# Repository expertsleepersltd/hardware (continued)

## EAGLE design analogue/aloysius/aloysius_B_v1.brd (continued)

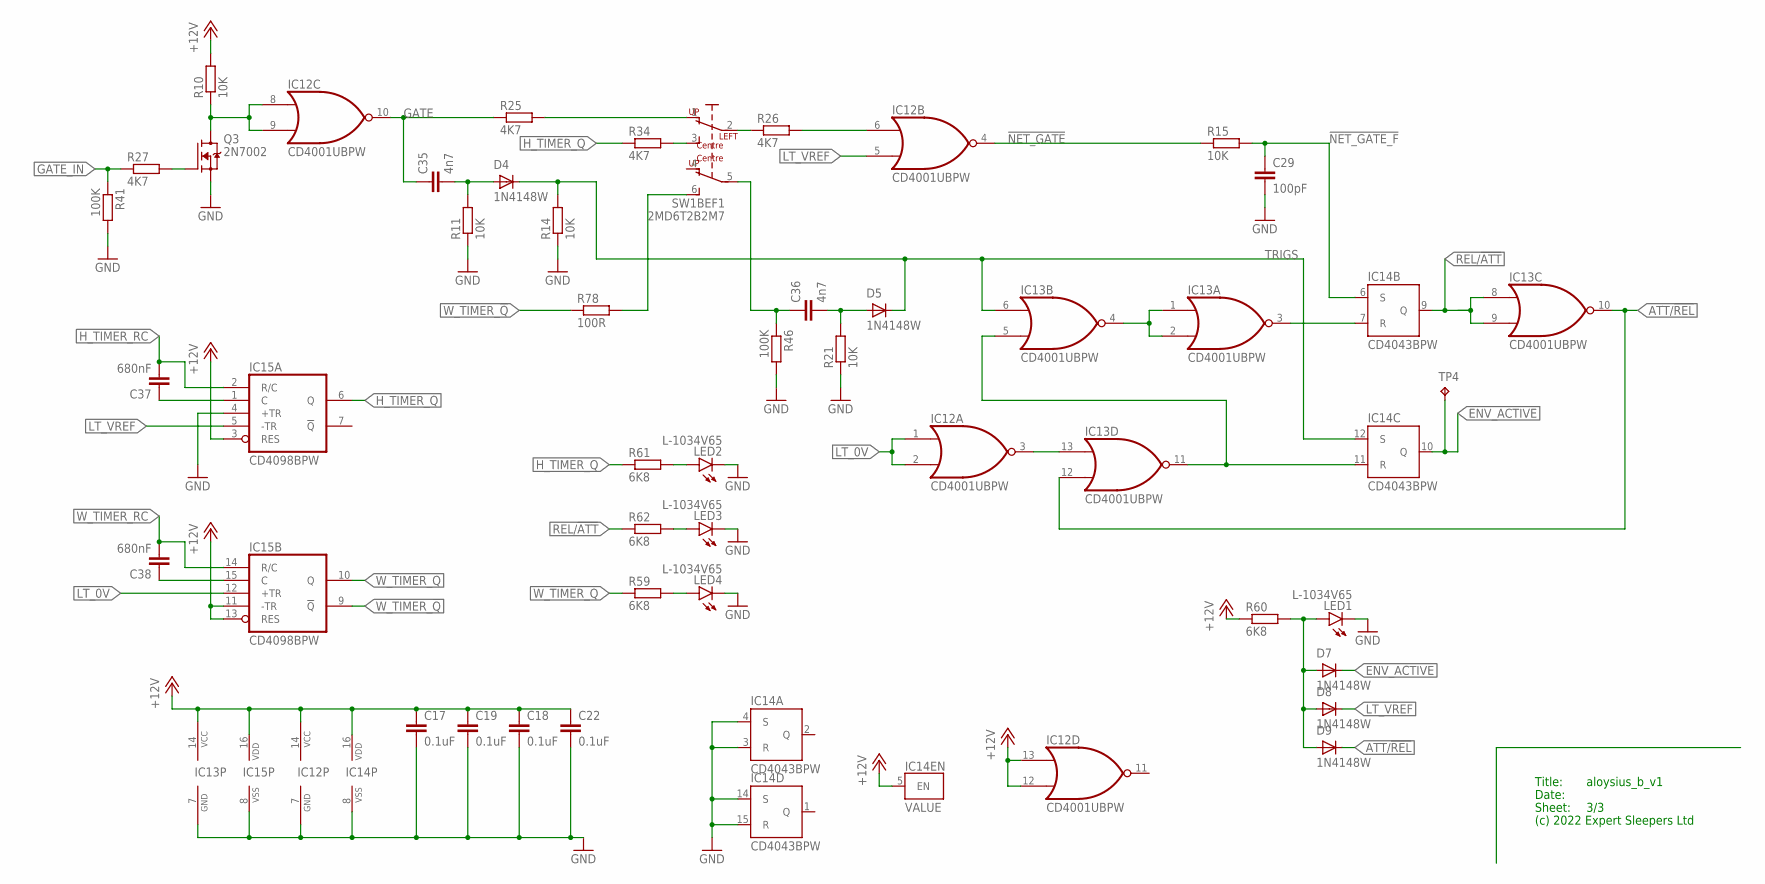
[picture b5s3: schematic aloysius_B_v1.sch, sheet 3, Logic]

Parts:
C17, C18, C19, C22: 0.1uF; C0402
C29: 100pF; C0603
C35, C36: 4n7; C0603
C37, C38: 680nF; C0603
D4, D5, D7, D8, D9: 1N4148W; SOD123
IC12, IC13: CD4001UBPW; TSSOP14
IC14: CD4043BPW; TSSOP16
IC15: CD4098BPW; TSSOP16
LED1, LED2, LED3, LED4: L-1034V65; L-1034_V6.5MM
Q3: 2N7002; SOT23
R10, R11, R14, R15, R21: 10K; R0603
R25, R26, R27, R34: 4K7; R0603
R41, R46: 100K; R0603
R59, R60, R61, R62: 6K8; R0603
R78: 100R; R0603
SW1: 2MD6T2B2M7; 2MD1T2B2M7RE
TP4: RA2; P1-13

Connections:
!NET_GATE: IC12.4 (O), R15.1
!NET_GATE_F: C29.1, IC14.6 (S), R15.2
+12V: C17.1, C18.1, C19.1, C22.1, IC12.12 (I1), IC12.13 (I0), IC12.14 (VCC), IC13.14 (VCC), IC14.5 (EN), IC14.16 (VDD), IC15.3 (RES), IC15.11 (-TR), IC15.13 (RES), IC15.16 (VDD), R10.2, R60.1; also elsewhere on the board
ATT/!REL: D9.C, IC13.10 (O), IC13.12 (I1); also elsewhere on the board
ENV_ACTIVE: D7.C, IC14.10 (Q), TP4.TP; also elsewhere on the board
GATE: C35.1, IC12.10 (O), R25.1
GATE_IN: R27.1, R41.1; also elsewhere on the board
GATE_SW: R25.2, SW1.1 (LU)
GND: C17.2, C18.2, C19.2, C22.2, C29.2, IC12.7 (GND), IC13.7 (GND), IC14.3 (R), IC14.4 (S), IC14.8 (VSS), IC14.14 (S), IC14.15 (R), IC15.4 (+TR), IC15.8 (VSS), LED1.K (C), LED2.K (C), LED3.K (C), LED4.K (C), Q3.2 (S), R11.1, R14.1, R21.1, R41.2, R46.2; also elsewhere on the board
H_TIMER_Q: IC15.6 (Q), R34.1, R61.1
H_TIMER_RC: C37.2, IC15.2 (R/C); also elsewhere on the board
LT_0V: IC12.1 (I0), IC12.2 (I1), IC15.12 (+TR); also elsewhere on the board
LT_VREF: D8.C, IC12.5 (I1), IC15.5 (-TR); also elsewhere on the board
unnamed: R34.2, SW1.3 (LD)
unnamed: C36.2, D5.A, R21.2
unnamed: C37.1, IC15.1 (C)
unnamed: IC12.6 (I0), R26.2
unnamed: IC12.3 (O), IC13.13 (I0)
unnamed: C38.1, IC15.15 (C)
unnamed: LED4.A, R59.2
unnamed: C35.2, D4.A, R11.2
unnamed: IC12.8 (I0), IC12.9 (I1), Q3.3 (D), R10.1
unnamed: Q3.1 (G), R27.2
unnamed: R26.1, SW1.2 (PL)
unnamed: IC13.3 (O), IC14.7 (R)
unnamed: LED2.A, R61.2
unnamed: IC13.5 (I1), IC13.11 (O), IC14.11 (R)
unnamed: LED3.A, R62.2
unnamed: IC13.1 (I0), IC13.2 (I1), IC13.4 (O)
unnamed: D7.A, D8.A, D9.A, LED1.A, R60.2
REL/!ATT: IC13.8 (I0), IC13.9 (I1), IC14.9 (Q), R62.1; also elsewhere on the board
RETRIG: R78.2, SW1.6 (RD)
RETRIG_SW: C36.1, R46.1, SW1.5 (PR)
TRIGS: D4.C, D5.C, IC13.6 (I0), IC14.12 (S), R14.2
W_TIMER_!Q: IC15.9 (!Q), R78.1
W_TIMER_Q: IC15.10 (Q), R59.1
W_TIMER_RC: C38.2, IC15.14 (R/C); also elsewhere on the board

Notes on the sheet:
Title:
Date:
Sheet:
(c) 2022 Expert Sleepers Ltd

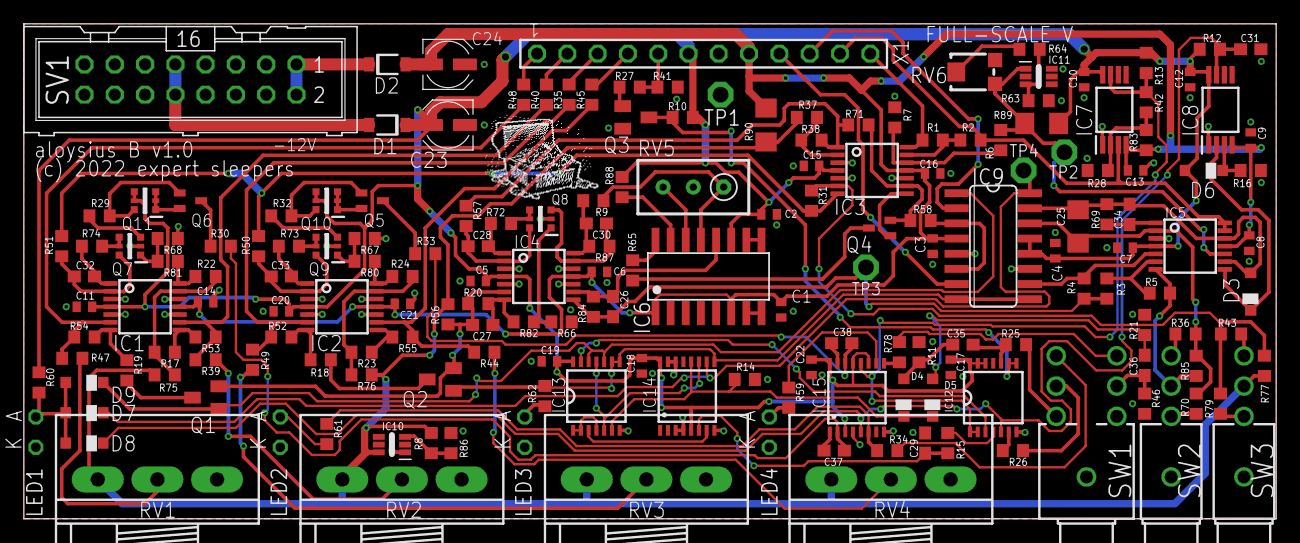
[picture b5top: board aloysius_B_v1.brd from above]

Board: 2 copper layers, 105.0 x 41.5 mm, 183 parts (0 on the bottom side), 126 nets.

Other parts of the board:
U$2: TREASURE_10MM_300DPI

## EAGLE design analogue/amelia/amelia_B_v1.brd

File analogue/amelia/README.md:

Amelia
======

https://expert-sleepers.co.uk/amelia.html

Copyright (c) 2023 Expert Sleepers Ltd

Please refer to [LICENSE.md](LICENSE.md) for licensing information.

Please note that Expert Sleepers® is a registered trade mark in the UK and the European Union. Remove any branding before making a derivative work.

Front panel layout is [here](../../panels).

Board and schematic are in [EAGLE](https://en.wikipedia.org/wiki/EAGLE_(program)) format.

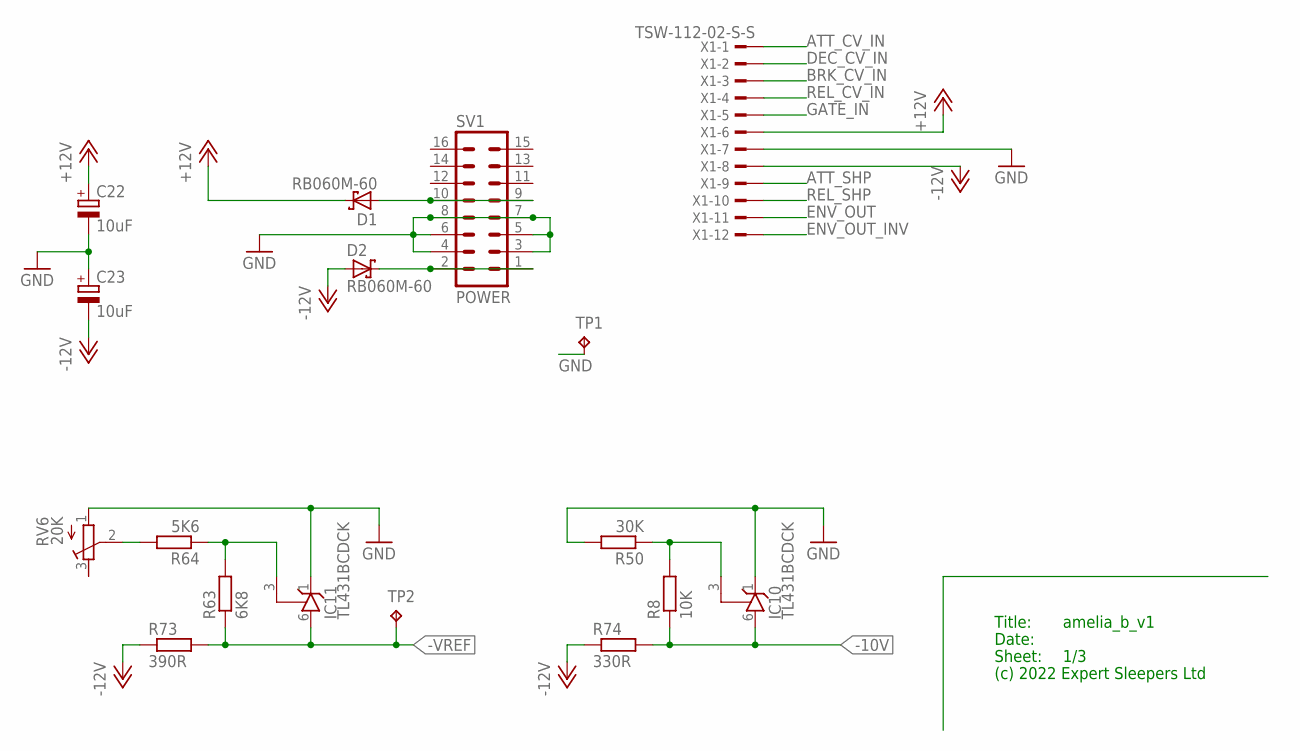
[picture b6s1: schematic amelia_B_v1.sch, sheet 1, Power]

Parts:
C22, C23: 10uF; UD-4X5,8_NICHICON
D1, D2: RB060M-60; SOD123FL
IC10, IC11: TL431BCDCK; DCK_SC-70
R8: 10K; R0603
R50: 30K; R0603
R63: 6K8; R0603
R64: 5K6; R0603
R73: 390R; R1206
R74: 330R; R1206
RV6: 20K; TC33X
SV1: POWER; ML16
TP1, TP2: RA2; P1-13
X1: TSW-112-02-S-S

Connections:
+12V: C22.+, D1.C, X1.6; also elsewhere on the board
-10V: IC10.6 (A), R8.1, R74.2; also elsewhere on the board
-12V: C23.-, D2.A, R73.1, R74.1, X1.8; also elsewhere on the board
-VREF: IC11.6 (A), R63.1, R73.2, TP2.TP; also elsewhere on the board
ATT_CV_IN: X1.1; also elsewhere on the board
ATT_SHP: X1.9; also elsewhere on the board
BRK_CV_IN: X1.3; also elsewhere on the board
DEC_CV_IN: X1.2; also elsewhere on the board
ENV_OUT: X1.11; also elsewhere on the board
ENV_OUT_INV: X1.12; also elsewhere on the board
GATE_IN: X1.5; also elsewhere on the board
GND: C22.-, C23.+, IC10.1 (C), IC11.1 (C), R50.2, RV6.1 (A), SV1.3, SV1.4, SV1.5, SV1.6, SV1.7, SV1.8, TP1.TP, X1.7; also elsewhere on the board
unnamed: D2.C, SV1.1, SV1.2
unnamed: D1.A, SV1.9, SV1.10
unnamed: IC11.3 (R), R63.2, R64.1
unnamed: R64.2, RV6.2 (S)
unnamed: IC10.3 (R), R8.2, R50.1
REL_CV_IN: X1.4; also elsewhere on the board
REL_SHP: X1.10; also elsewhere on the board

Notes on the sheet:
Title:
Date:
Sheet:
(c) 2022 Expert Sleepers Ltd

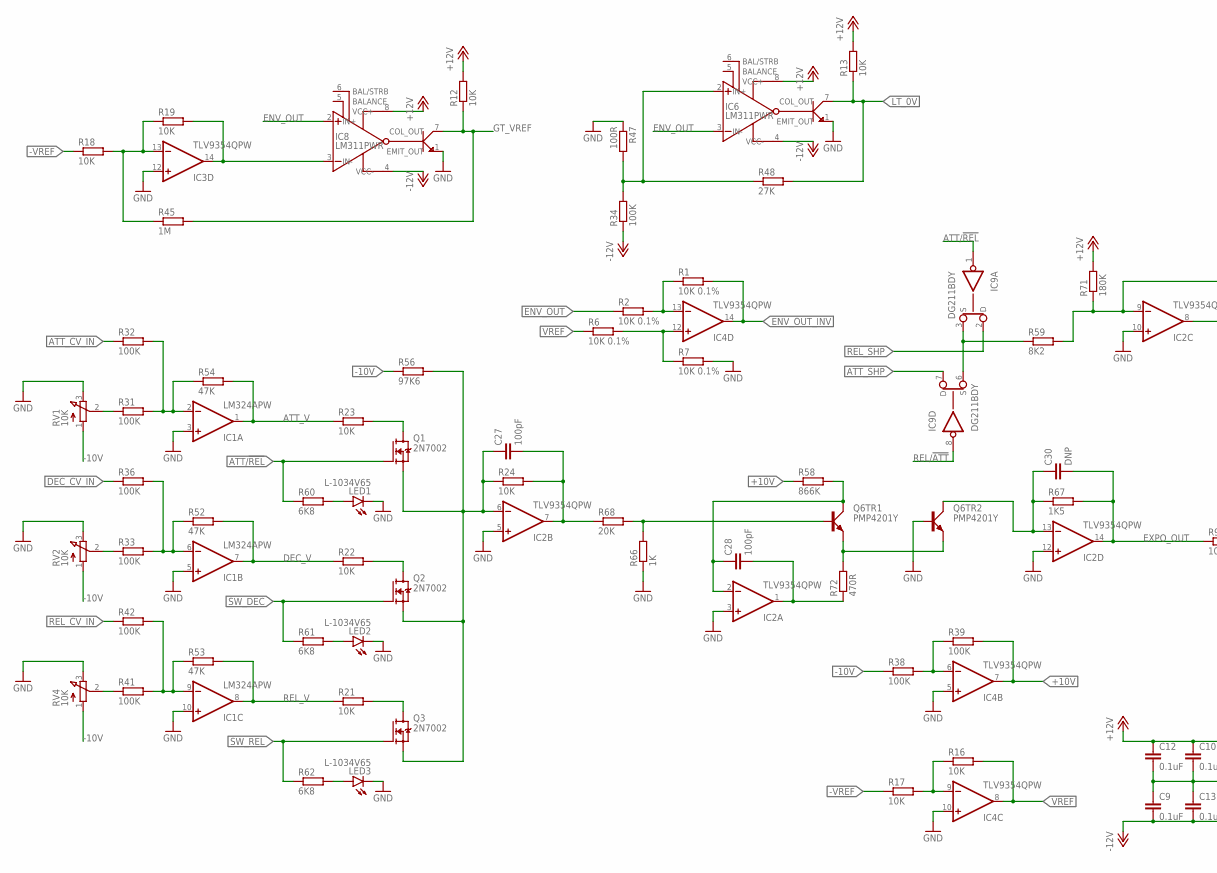
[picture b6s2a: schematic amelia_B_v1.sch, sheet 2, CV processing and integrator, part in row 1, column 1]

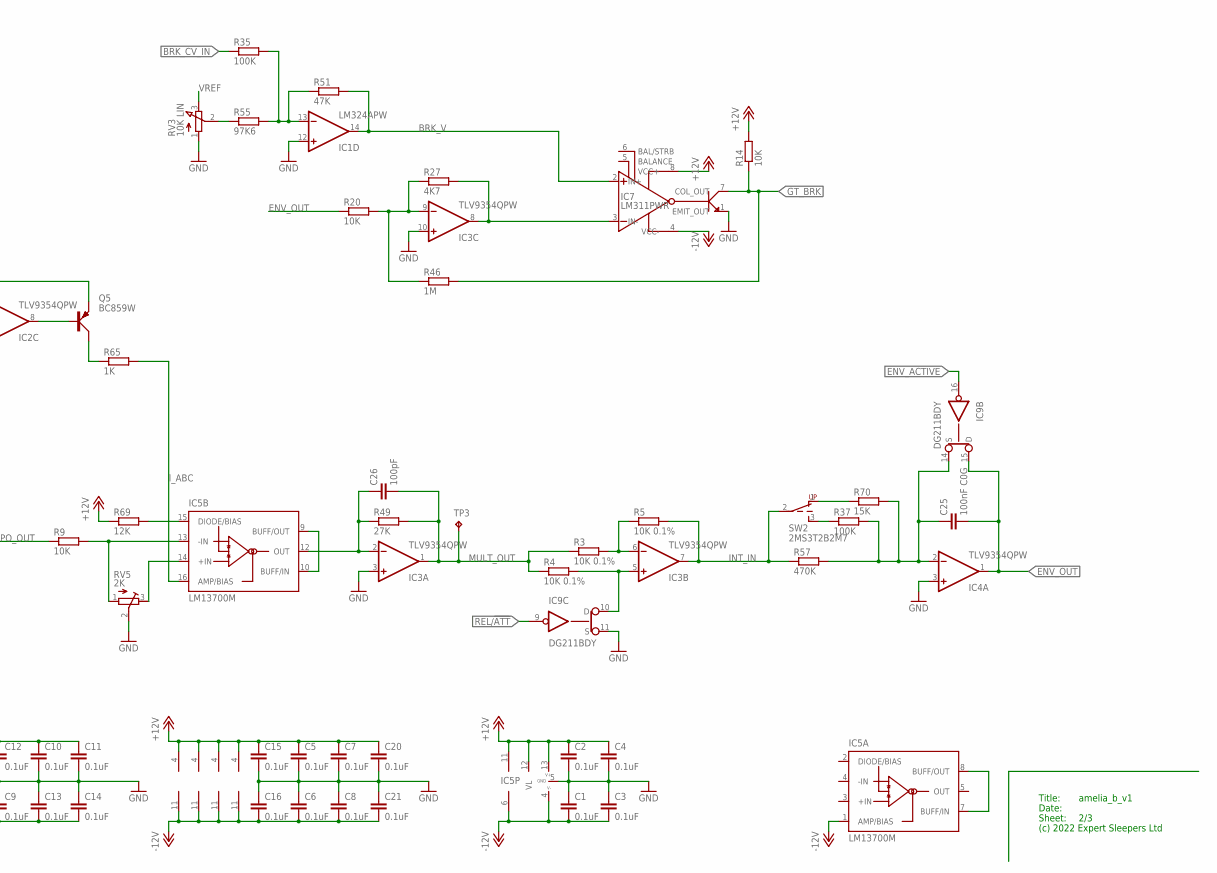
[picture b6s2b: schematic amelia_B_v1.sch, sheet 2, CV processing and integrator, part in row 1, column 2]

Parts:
C1, C2, C3, C4, C5, C6, C7, C8, C9, C10, C11, C12, C13, C14, C15, C16, C20, C21: 0.1uF; C0402
C25: 100nF C0G; C1206
C26, C27, C28: 100pF; C0603
C30: DNP; C0603
IC1: LM324APW; PW_R-PDSO-G14
IC2, IC3, IC4: TLV9354QPW; PW_R-PDSO-G14
IC5: LM13700M; SO16
IC6, IC7, IC8: LM311PWR; SOP65P640X120-8N
IC9: DG211BDY; SO16
LED1, LED2, LED3: L-1034V65; L-1034_V6.5MM
Q1, Q2, Q3: 2N7002; SOT23
Q5: BC859W; SOT323
Q6: PMP4201Y; SOT65P210X110-6N
R1, R2, R3, R4, R5, R6, R7: 10K 0.1%; R0603
R9, R12, R13, R14, R16, R17, R18, R19, R20, R21, R22, R23, R24: 10K; R0603
R27: 4K7; R0603
R31, R32, R33, R34, R35, R36, R37, R38, R39, R41, R42: 100K; R0603
R45, R46: 1M; R0603
R47: 100R; R0603
R48, R49: 27K; R0603
R51, R52, R53, R54: 47K; R0603
R55, R56: 97K6; R0603
R57: 470K; R0603
R58: 866K; R0603
R59: 8K2; R0603
R60, R61, R62: 6K8; R0603
R65, R66: 1K; R0603
R67: 1K5; R0603
R68: 20K; R0603
R69: 12K; R0603
R70: 15K; R0603
R71: 180K; R0603
R72: 470R; R0603
RV1, RV2, RV4: 10K; RD1610NOA0X
RV3: 10K LIN; RD1610NOA0X
RV5: 2K; RTRIM3296W
SW2: 2MS3T2B2M7; 2MS1T2B2M7RE
TP3: RA2; P1-13

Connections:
+10V: IC4.7 (OUT), R39.2, R58.1
+12V: C2.1, C4.1, C5.1, C7.1, C10.1, C11.1, C12.1, C15.1, C20.1, IC1.4 (V+), IC2.4 (V+), IC3.4 (V+), IC4.4 (V+), IC5.11 (V+), IC6.8 (VCC+), IC7.8 (VCC+), IC8.8 (VCC+), IC9.12 (VL), IC9.13 (V+), R12.2, R13.2, R14.2, R69.1, R71.2; also elsewhere on the board
-10V: R38.1, R56.1, RV1.1 (A), RV2.1 (A), RV4.1 (A); also elsewhere on the board
-12V: C1.2, C3.2, C6.2, C8.2, C9.2, C13.2, C14.2, C16.2, C21.2, IC1.11 (V-), IC2.11 (V-), IC3.11 (V-), IC4.11 (V-), IC5.1 (AMP/BIAS), IC5.6 (V-), IC6.4 (VCC-), IC7.4 (VCC-), IC8.4 (VCC-), IC9.4 (V-), R34.1; also elsewhere on the board
-VREF: R17.1, R18.1; also elsewhere on the board
ATT/!REL: IC9.1 (IN), Q1.1 (G), R60.1; also elsewhere on the board
ATT_CV_IN: R32.1; also elsewhere on the board
ATT_SHP: IC9.7 (D); also elsewhere on the board
ATT_V: IC1.1 (OUT), R23.1, R54.2
BRK_CV_IN: R35.1; also elsewhere on the board
BRK_V: IC1.14 (OUT), IC7.2 (IN+), R51.2
DEC_CV_IN: R36.1; also elsewhere on the board
DEC_V: IC1.7 (OUT), R22.1, R52.2
ENV_ACTIVE: IC9.16 (IN); also elsewhere on the board
ENV_OUT: C25.2, IC4.1 (OUT), IC6.3 (IN-), IC8.2 (IN+), IC9.15 (D), R2.1, R20.1; also elsewhere on the board
ENV_OUT_INV: IC4.14 (OUT), R1.2; also elsewhere on the board
EXPO_OUT: C30.2, IC2.14 (OUT), R9.1, R67.2
GND: C1.1, C2.2, C3.1, C4.2, C5.2, C6.1, C7.2, C8.1, C9.1, C10.2, C11.2, C12.2, C13.1, C14.1, C15.2, C16.1, C20.2, C21.1, IC1.3 (+IN), IC1.5 (+IN), IC1.10 (+IN), IC1.12 (+IN), IC2.3 (+IN), IC2.5 (+IN), IC2.10 (+IN), IC2.12 (+IN), IC3.3 (+IN), IC3.10 (+IN), IC3.12 (+IN), IC4.3 (+IN), IC4.5 (+IN), IC4.10 (+IN), IC6.1 (EMIT_OUT), IC7.1 (EMIT_OUT), IC8.1 (EMIT_OUT), IC9.5 (GND), IC9.11 (S), LED1.K (C), LED2.K (C), LED3.K (C), Q6.2 (B), R7.2, R47.1, R66.1, RV1.3 (E), RV2.3 (E), RV3.1 (A), RV4.3 (E), RV5.2 (S); also elsewhere on the board
GT_BRK: IC7.7 (COL_OUT), R14.1, R46.2; also elsewhere on the board
GT_VREF: IC8.7 (COL_OUT), R12.1, R45.2; also elsewhere on the board
INT_IN: IC3.7 (OUT), R5.2, R57.1, SW2.2 (PR)
I_ABC: IC5.16 (AMP/BIAS), R65.2
LT_0V: IC6.7 (COL_OUT), R13.1, R48.2; also elsewhere on the board
MULT_OUT: C26.2, IC3.1 (OUT), R3.1, R4.1, R49.2, TP3.TP
unnamed: IC4.13 (-IN), R1.1, R2.2
unnamed: C30.1, IC2.13 (-IN), Q6.3 (C), R67.1
unnamed: C26.1, IC3.2 (-IN), IC5.12 (OUT), R49.1
unnamed: IC5.15 (DIODE/BIAS), R69.2
unnamed: IC3.6 (-IN), R3.2, R5.1
unnamed: IC5.13 (-IN), R9.2, RV5.1 (A)
unnamed: IC5.7 (BUFF/IN), IC5.8 (BUFF/OUT)
unnamed: IC3.13 (-IN), R18.2, R19.1, R45.1
unnamed: IC3.14 (OUT), IC8.3 (IN-), R19.2
unnamed: R41.1, RV4.2 (S)
unnamed: IC1.9 (-IN), R41.2, R42.2, R53.1
unnamed: Q1.3 (D), R23.2
unnamed: C27.2, IC2.7 (OUT), R24.2, R68.1
unnamed: R55.1, RV3.2 (S)
unnamed: IC4.9 (-IN), R16.1, R17.2
unnamed: IC4.12 (+IN), R6.2, R7.1
unnamed: IC3.9 (-IN), R20.2, R27.1, R46.1
unnamed: IC6.2 (IN+), R34.2, R47.2, R48.1
unnamed: IC3.8 (OUT), IC7.3 (IN-), R27.2
unnamed: C25.1, IC4.2 (-IN), IC9.14 (S), R37.2, R57.2, R70.2
unnamed: IC2.8 (OUT), Q5.1 (B)
unnamed: IC3.5 (+IN), IC9.10 (D), R4.2
unnamed: R31.1, RV1.2 (S)
unnamed: Q2.3 (D), R22.2
unnamed: IC1.13 (-IN), R35.2, R51.1, R55.2
unnamed: Q3.3 (D), R21.2
unnamed: C27.1, IC2.6 (-IN), Q1.2 (S), Q2.2 (S), Q3.2 (S), R24.1, R56.2
unnamed: Q6.1 (B), R66.2, R68.2
unnamed: IC5.14 (+IN), RV5.3 (E)
unnamed: IC1.2 (-IN), R31.2, R32.2, R54.1
unnamed: R33.1, RV2.2 (S)
unnamed: IC1.6 (-IN), R33.2, R36.2, R52.1
unnamed: R37.1, SW2.3 (RD)
unnamed: C28.1, IC2.2 (-IN), Q6.6 (C), R58.2
unnamed: C28.2, IC2.1 (OUT), R72.1
unnamed: IC2.9 (-IN), Q5.2 (E), R59.2, R71.1
unnamed: R70.1, SW2.1 (RU)
unnamed: Q6.4 (E), Q6.5 (E), R72.2
unnamed: IC4.6 (-IN), R38.2, R39.1
unnamed: LED1.A, R60.2
unnamed: LED2.A, R61.2
unnamed: LED3.A, R62.2
unnamed: Q5.3 (C), R65.1
unnamed: IC9.3 (S), IC9.6 (S), R59.1
unnamed: IC5.9 (BUFF/OUT), IC5.10 (BUFF/IN)
REL/!ATT: IC9.8 (IN), IC9.9 (IN); also elsewhere on the board
REL_CV_IN: R42.1; also elsewhere on the board
REL_SHP: IC9.2 (D); also elsewhere on the board
REL_V: IC1.8 (OUT), R21.1, R53.2
SW_DEC: Q2.1 (G), R61.1; also elsewhere on the board
SW_REL: Q3.1 (G), R62.1; also elsewhere on the board
VREF: IC4.8 (OUT), R6.1, R16.2, RV3.3 (E)

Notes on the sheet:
Title:
Date:
Sheet:
(c) 2022 Expert Sleepers Ltd

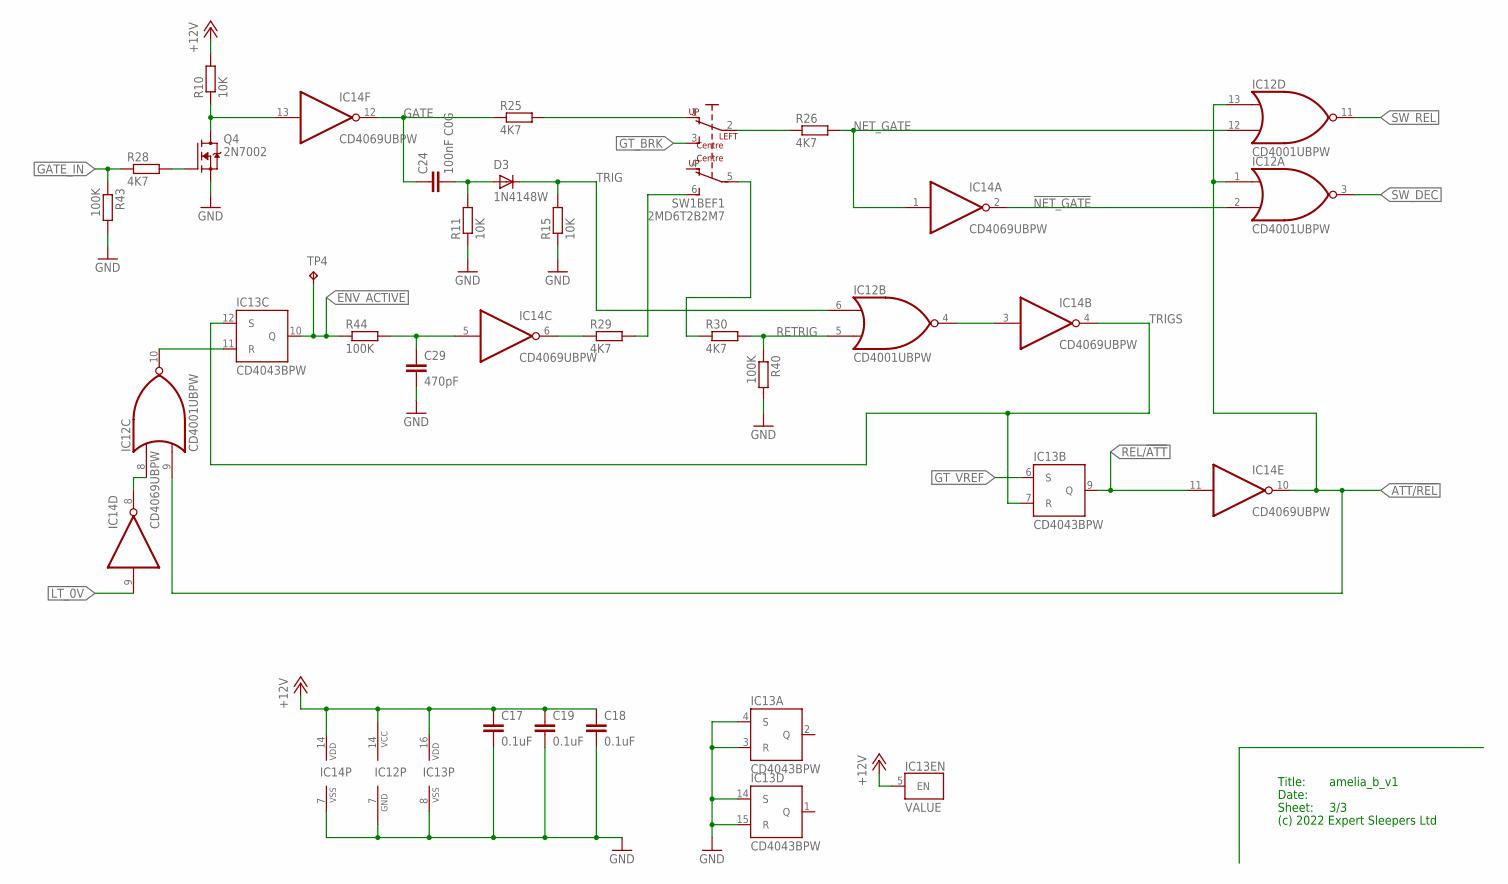
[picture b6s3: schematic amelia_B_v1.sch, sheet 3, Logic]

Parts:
C17, C18, C19: 0.1uF; C0402
C24: 100nF C0G; C1206
C29: 470pF; C0603
D3: 1N4148W; SOD123
IC12: CD4001UBPW; TSSOP14
IC13: CD4043BPW; TSSOP16
IC14: CD4069UBPW; TSSOP14
Q4: 2N7002; SOT23
R10, R11, R15: 10K; R0603
R25, R26, R28, R29, R30: 4K7; R0603
R40, R43, R44: 100K; R0603
SW1: 2MD6T2B2M7; 2MD1T2B2M7RE
TP4: RA2; P1-13

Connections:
!NET_GATE: IC12.2 (I1), IC14.2 (O)
+12V: C17.1, C18.1, C19.1, IC12.14 (VCC), IC13.5 (EN), IC13.16 (VDD), IC14.14 (VDD), R10.2; also elsewhere on the board
ATT/!REL: IC12.1 (I0), IC12.9 (I1), IC12.13 (I0), IC14.10 (O); also elsewhere on the board
ENV_ACTIVE: IC13.10 (Q), R44.1, TP4.TP; also elsewhere on the board
GATE: C24.1, IC14.12 (O), R25.1
GATE_IN: R28.1, R43.1; also elsewhere on the board
GATE_SW: R25.2, SW1.1 (LU)
GND: C17.2, C18.2, C19.2, C29.2, IC12.7 (GND), IC13.3 (R), IC13.4 (S), IC13.8 (VSS), IC13.14 (S), IC13.15 (R), IC14.7 (VSS), Q4.2 (S), R11.1, R15.1, R40.2, R43.2; also elsewhere on the board
GT_BRK: SW1.3 (LD); also elsewhere on the board
GT_VREF: IC13.6 (S); also elsewhere on the board
LT_0V: IC14.9 (I); also elsewhere on the board
unnamed: C29.1, IC14.5 (I), R44.2
unnamed: IC14.6 (O), R29.1
unnamed: IC12.8 (I0), IC14.8 (O)
unnamed: IC12.4 (O), IC14.3 (I)
unnamed: C24.2, D3.A, R11.2
unnamed: IC14.13 (I), Q4.3 (D), R10.1
unnamed: Q4.1 (G), R28.2
unnamed: R26.1, SW1.2 (PL)
unnamed: R29.2, SW1.6 (RD)
unnamed: IC12.10 (O), IC13.11 (R)
NET_GATE: IC12.12 (I1), IC14.1 (I), R26.2
REL/!ATT: IC13.9 (Q), IC14.11 (I); also elsewhere on the board
RETRIG: IC12.5 (I1), R30.2, R40.1
RETRIG_SW: R30.1, SW1.5 (PR)
SW_DEC: IC12.3 (O); also elsewhere on the board
SW_REL: IC12.11 (O); also elsewhere on the board
TRIG: D3.C, IC12.6 (I0), R15.2
TRIGS: IC13.7 (R), IC13.12 (S), IC14.4 (O)

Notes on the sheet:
Title:
Date:
Sheet:
(c) 2022 Expert Sleepers Ltd

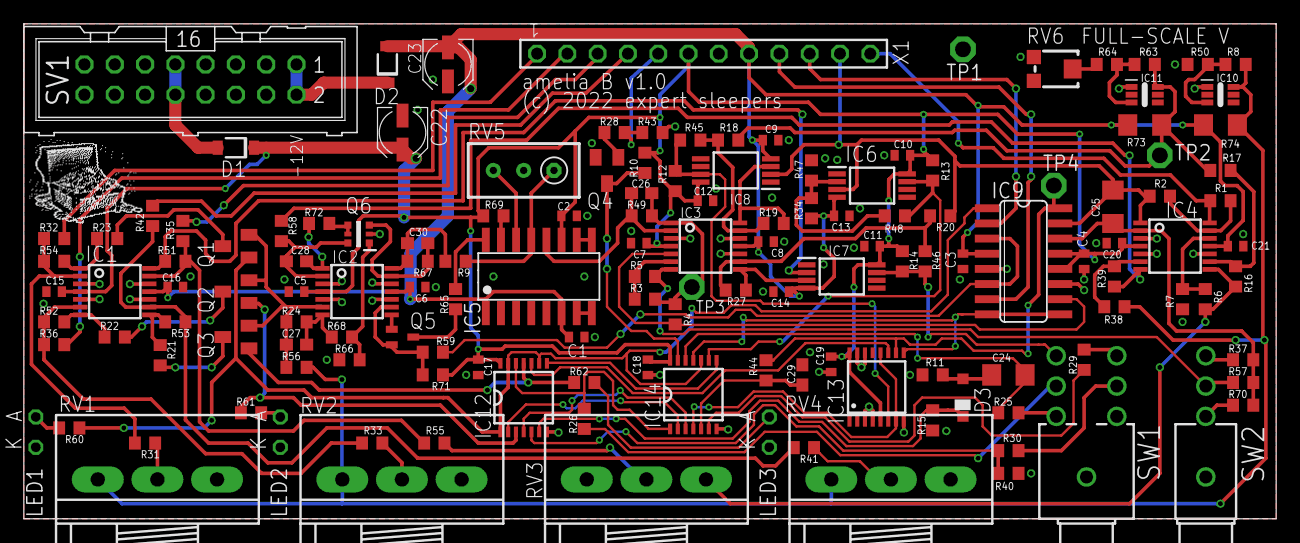
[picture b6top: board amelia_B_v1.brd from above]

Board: 2 copper layers, 105.0 x 41.5 mm, 145 parts (0 on the bottom side), 100 nets.

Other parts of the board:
U$2: TREASURE_10MM_300DPI

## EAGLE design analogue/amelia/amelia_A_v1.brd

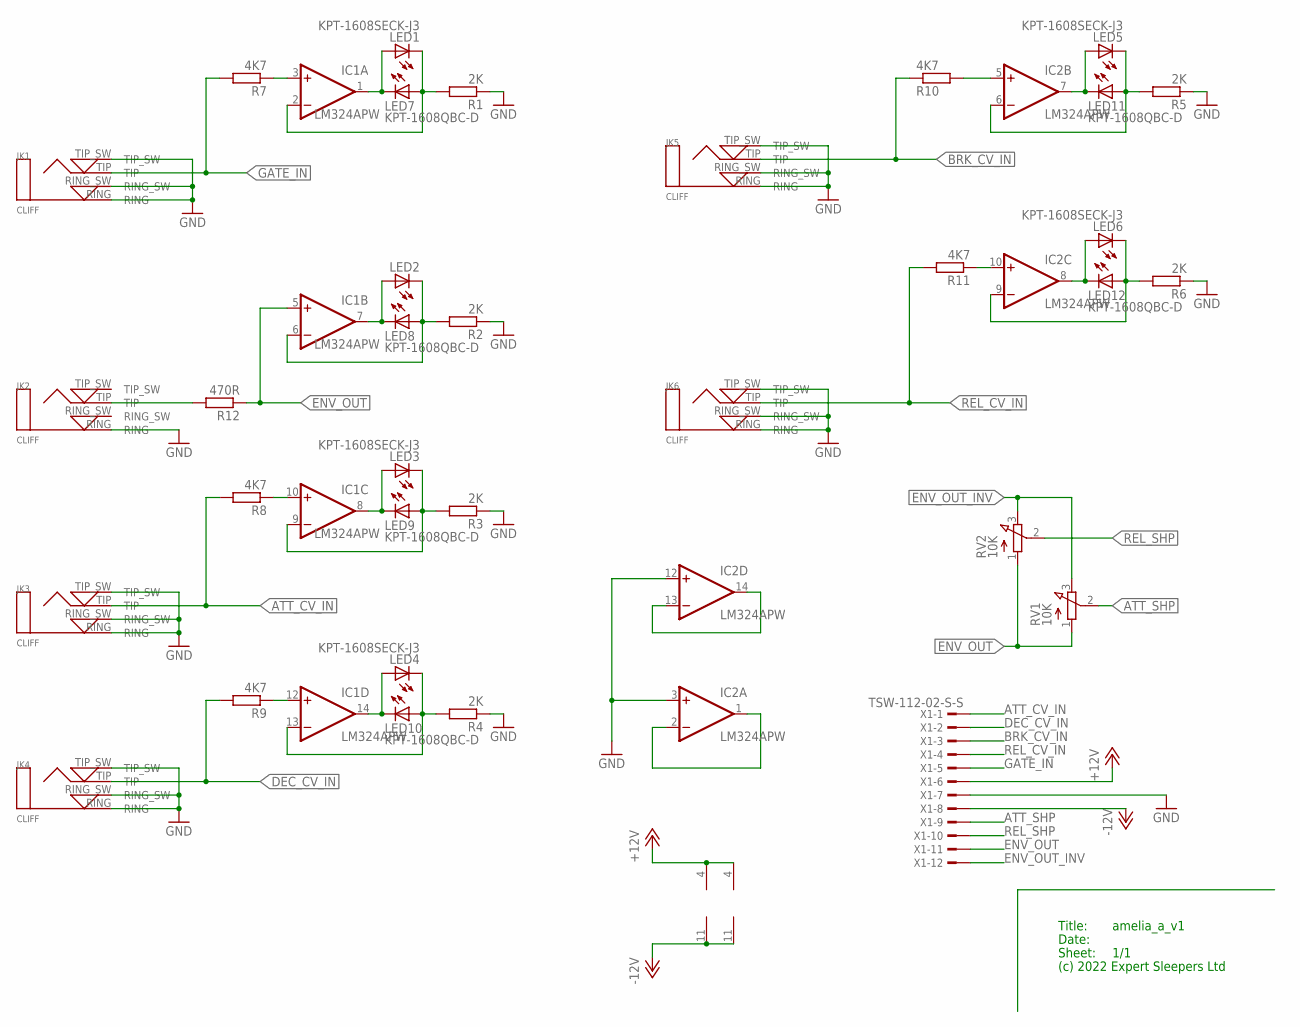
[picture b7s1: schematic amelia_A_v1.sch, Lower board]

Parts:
IC1, IC2: LM324APW; PW_R-PDSO-G14
JK1, JK2, JK3, JK4, JK5, JK6: CLIFF; CLIFF3.5MMPCB
LED1, LED2, LED3, LED4, LED5, LED6: KPT-1608SECK-J3; CHIPLED_0603_LEFT
LED7, LED8, LED9, LED10, LED11, LED12: KPT-1608QBC-D; CHIPLED_0603_RIGHT
R1, R2, R3, R4, R5, R6: 2K; R1206
R7, R8, R9, R10, R11: 4K7; R1206
R12: 470R; R1206
RV1, RV2: 10K; RA0901NOX0A-VA1-131
X1: TSW-112-02-S-S

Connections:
+12V: IC1.4 (V+), IC2.4 (V+), X1.6
-12V: IC1.11 (V-), IC2.11 (V-), X1.8
ATT_CV_IN: JK3.TIP, R8.2, X1.1
ATT_SHP: RV1.2 (S), X1.9
BRK_CV_IN: JK5.TIP, R10.1, X1.3
DEC_CV_IN: JK4.TIP, R9.2, X1.2
ENV_OUT: IC1.5 (+IN), R12.1, RV1.1 (A), RV2.1 (A), X1.11
ENV_OUT_INV: RV1.3 (E), RV2.3 (E), X1.12
GATE_IN: JK1.TIP, R7.2, X1.5
GND: IC2.3 (+IN), IC2.12 (+IN), JK1.RING, JK1.RING_SW, JK1.TIP_SW, JK2.RING, JK3.RING, JK3.RING_SW, JK3.TIP_SW, JK4.RING, JK4.RING_SW, JK4.TIP_SW, JK5.RING, JK5.RING_SW, JK5.TIP_SW, JK6.RING, JK6.RING_SW, JK6.TIP_SW, R1.1, R2.1, R3.1, R4.1, R5.1, R6.1, X1.7
unnamed: IC1.10 (+IN), R8.1
unnamed: IC1.13 (-IN), LED4.1 (C), LED10.1 (A), R4.2
unnamed: IC1.14 (OUT), LED4.2 (A), LED10.2 (C)
unnamed: IC2.1 (OUT), IC2.2 (-IN)
unnamed: IC1.12 (+IN), R9.1
unnamed: IC1.8 (OUT), LED3.2 (A), LED9.2 (C)
unnamed: IC1.9 (-IN), LED3.1 (C), LED9.1 (A), R3.2
unnamed: IC1.1 (OUT), LED1.2 (A), LED7.2 (C)
unnamed: IC1.2 (-IN), LED1.1 (C), LED7.1 (A), R1.2
unnamed: IC1.3 (+IN), R7.1
unnamed: IC1.7 (OUT), LED2.2 (A), LED8.2 (C)
unnamed: IC1.6 (-IN), LED2.1 (C), LED8.1 (A), R2.2
unnamed: IC2.5 (+IN), R10.2
unnamed: IC2.8 (OUT), LED6.2 (A), LED12.2 (C)
unnamed: IC2.9 (-IN), LED6.1 (C), LED12.1 (A), R6.2
unnamed: IC2.7 (OUT), LED5.2 (A), LED11.2 (C)
unnamed: IC2.6 (-IN), LED5.1 (C), LED11.1 (A), R5.2
unnamed: IC2.10 (+IN), R11.1
unnamed: JK2.TIP, R12.2
unnamed: IC2.13 (-IN), IC2.14 (OUT)
REL_CV_IN: JK6.TIP, R11.2, X1.4
REL_SHP: RV2.2 (S), X1.10

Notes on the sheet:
Title:
Date:
Sheet:
(c) 2022 Expert Sleepers Ltd

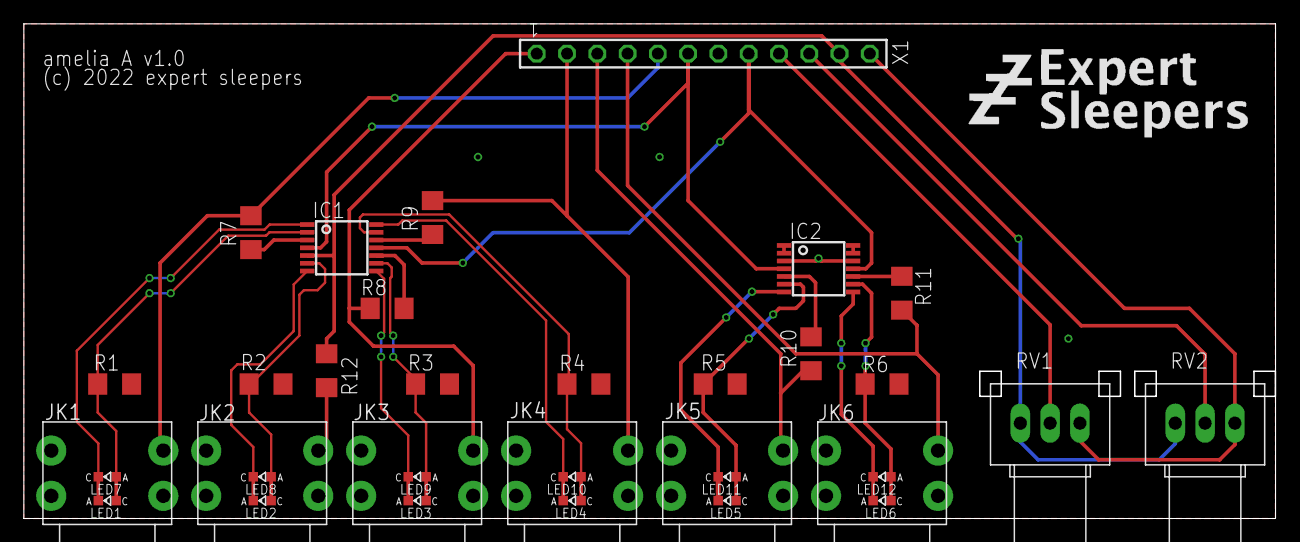
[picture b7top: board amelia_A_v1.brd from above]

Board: 2 copper layers, 104.9 x 41.4 mm, 36 parts (0 on the bottom side), 32 nets.

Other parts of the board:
U$1: ES_ZZZ_TEXT_TPLACE_1IN_600DPI

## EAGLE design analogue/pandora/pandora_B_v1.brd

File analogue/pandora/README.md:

Pandora
=======

https://expert-sleepers.co.uk/pandora.html

Copyright (c) 2022 Expert Sleepers Ltd

Please refer to [LICENSE.md](LICENSE.md) for licensing information.

Please note that Expert Sleepers® is a registered trade mark in the UK and the European Union. Remove any branding before making a derivative work.

Front panel layout is [here](../../panels).

Board and schematic are in [EAGLE](https://en.wikipedia.org/wiki/EAGLE_(program)) format.

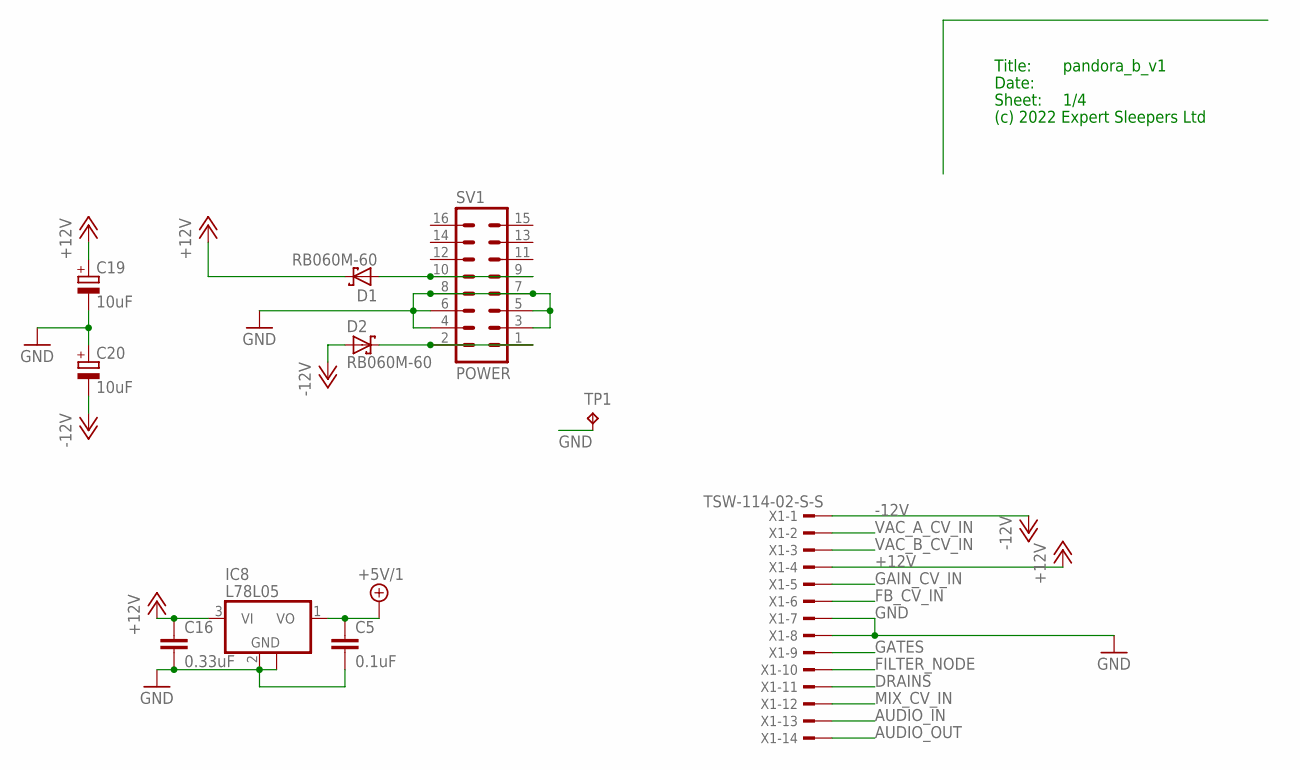
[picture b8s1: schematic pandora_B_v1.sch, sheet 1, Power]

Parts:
C5: 0.1uF; C0402
C16: 0.33uF; C0805
C19, C20: 10uF; UD-4X5,8_NICHICON
D1, D2: RB060M-60; SOD123FL
IC8: L78L05; SOT89
SV1: POWER; ML16
TP1: RA2; P1-13
X1: TSW-114-02-S-S

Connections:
+5V/1: C5.1, IC8.1 (VO); also elsewhere on the board
+12V: C16.1, C19.+, D1.C, IC8.3 (VI), X1.4; also elsewhere on the board
-12V: C20.-, D2.A, X1.1; also elsewhere on the board
AUDIO_IN: X1.13; also elsewhere on the board
AUDIO_OUT: X1.14; also elsewhere on the board
DRAINS: X1.11; also elsewhere on the board
FB_CV_IN: X1.6; also elsewhere on the board
FILTER_NODE: X1.10; also elsewhere on the board
GAIN_CV_IN: X1.5; also elsewhere on the board
GATES: X1.9; also elsewhere on the board
GND: C5.2, C16.2, C19.-, C20.+, IC8.2 (GND), IC8.2@1 (GND), SV1.3, SV1.4, SV1.5, SV1.6, SV1.7, SV1.8, TP1.TP, X1.7, X1.8; also elsewhere on the board
MIX_CV_IN: X1.12; also elsewhere on the board
unnamed: D2.C, SV1.1, SV1.2
unnamed: D1.A, SV1.9, SV1.10
VAC_A_CV_IN: X1.2; also elsewhere on the board
VAC_B_CV_IN: X1.3; also elsewhere on the board

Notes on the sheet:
Title:
Date:
Sheet:
(c) 2022 Expert Sleepers Ltd

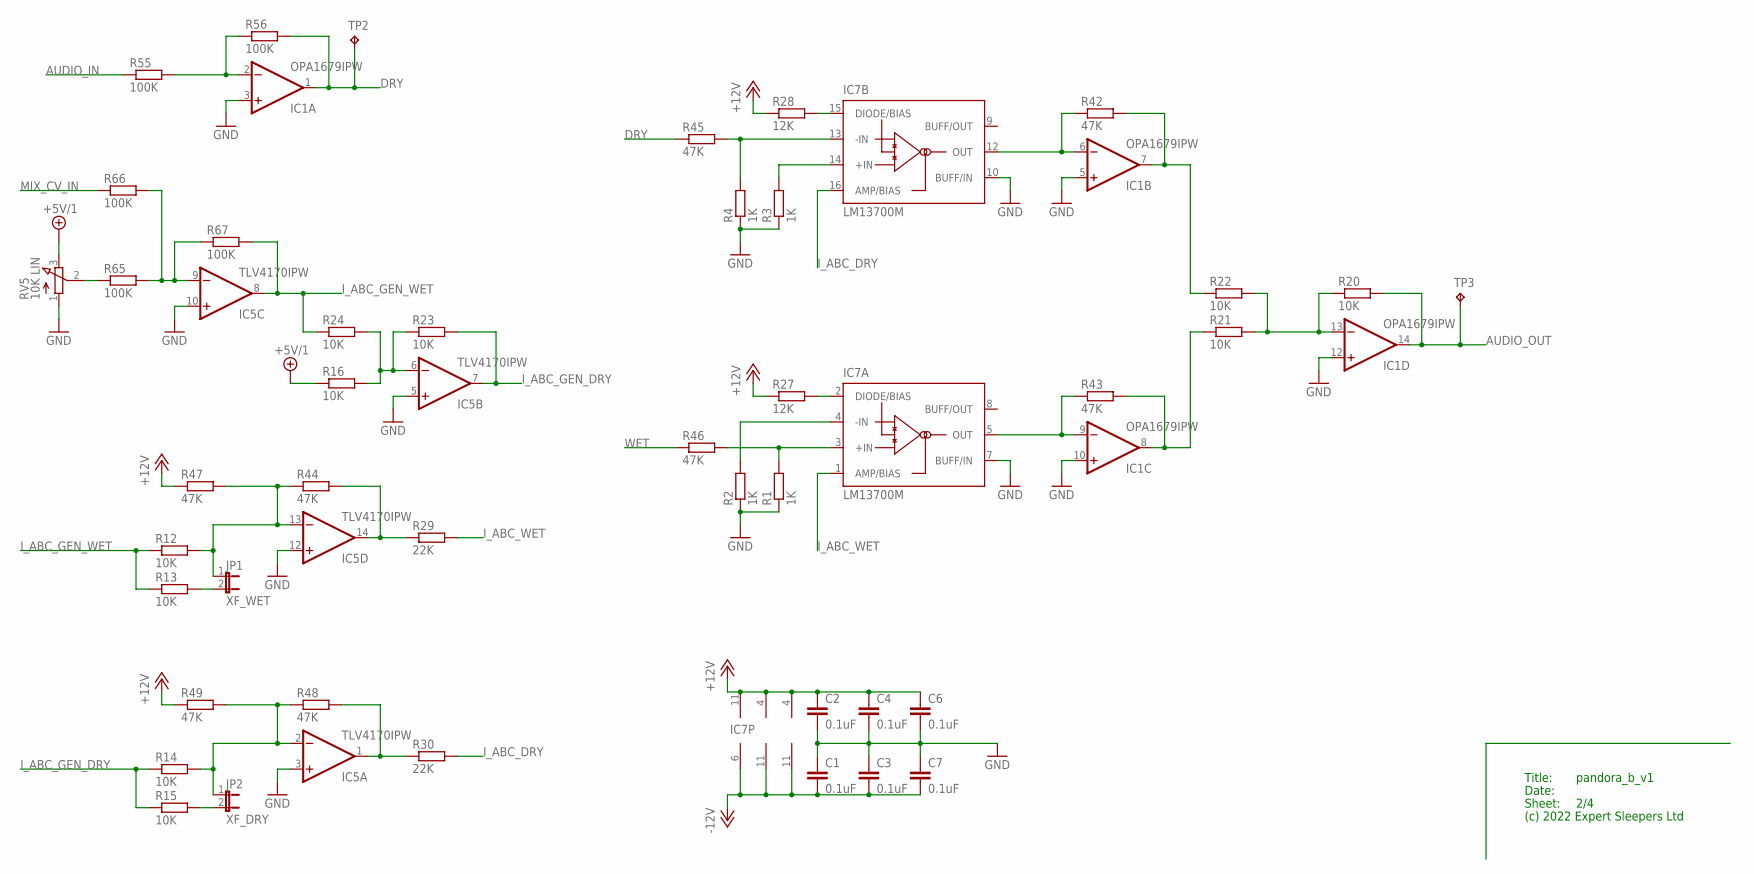
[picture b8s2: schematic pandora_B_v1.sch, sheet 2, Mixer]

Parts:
C1, C2, C3, C4, C6, C7: 0.1uF; C0402
IC1: OPA1679IPW; PW_R-PDSO-G14
IC5: TLV4170IPW; PW_R-PDSO-G14
IC7: LM13700M; SO16
JP1: XF_WET; JP1
JP2: XF_DRY; JP1
R1, R2, R3, R4: 1K; R0603
R12, R13, R14, R15, R16, R20, R21, R22, R23, R24: 10K; R0603
R27, R28: 12K; R0603
R29, R30: 22K; R0603
R42, R43, R44, R45, R46, R47, R48, R49: 47K; R0603
R55, R56, R65, R66, R67: 100K; R0603
RV5: 10K LIN; RD1610NOA0X
TP2, TP3: RA2; P1-13

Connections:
+5V/1: R16.1, RV5.3 (E); also elsewhere on the board
+12V: C2.1, C4.1, C6.1, IC1.4 (V+), IC5.4 (V+), IC7.11 (V+), R27.1, R28.1, R47.1, R49.1; also elsewhere on the board
-12V: C1.2, C3.2, C7.2, IC1.11 (V-), IC5.11 (V-), IC7.6 (V-); also elsewhere on the board
AUDIO_IN: R55.1; also elsewhere on the board
AUDIO_OUT: IC1.14 (OUT), R20.2, TP3.TP; also elsewhere on the board
DRY: IC1.1 (OUT), R45.1, R56.2, TP2.TP; also elsewhere on the board
GND: C1.1, C2.2, C3.1, C4.2, C6.2, C7.1, IC1.3 (+IN), IC1.5 (+IN), IC1.10 (+IN), IC1.12 (+IN), IC5.3 (+IN), IC5.5 (+IN), IC5.10 (+IN), IC5.12 (+IN), IC7.7 (BUFF/IN), IC7.10 (BUFF/IN), R1.1, R2.1, R3.1, R4.1, RV5.1 (A); also elsewhere on the board
I_ABC_DRY: IC7.16 (AMP/BIAS), R30.2
I_ABC_GEN_DRY: IC5.7 (OUT), R14.1, R15.1, R23.2
I_ABC_GEN_WET: IC5.8 (OUT), R12.1, R13.1, R24.1, R67.2
I_ABC_WET: IC7.1 (AMP/BIAS), R29.2
MIX_CV_IN: R66.1; also elsewhere on the board
unnamed: IC1.13 (-IN), R20.1, R21.2, R22.2
unnamed: R65.1, RV5.2 (S)
unnamed: IC7.15 (DIODE/BIAS), R28.2
unnamed: IC1.9 (-IN), IC7.5 (OUT), R43.1
unnamed: IC7.2 (DIODE/BIAS), R27.2
unnamed: IC1.6 (-IN), IC7.12 (OUT), R42.1
unnamed: IC1.8 (OUT), R21.1, R43.2
unnamed: IC5.9 (-IN), R65.2, R66.2, R67.1
unnamed: IC1.7 (OUT), R22.1, R42.2
unnamed: IC7.3 (+IN), R1.2, R46.2
unnamed: IC7.4 (-IN), R2.2
unnamed: IC5.13 (-IN), JP1.1, R12.2, R44.1, R47.2
unnamed: IC5.6 (-IN), R16.2, R23.1, R24.2
unnamed: IC5.14 (OUT), R29.1, R44.2
unnamed: IC5.1 (OUT), R30.1, R48.2
unnamed: IC5.2 (-IN), JP2.1, R14.2, R48.1, R49.2
unnamed: IC7.14 (+IN), R3.2
unnamed: IC7.13 (-IN), R4.2, R45.2
unnamed: IC1.2 (-IN), R55.2, R56.1
unnamed: JP2.2, R15.2
unnamed: JP1.2, R13.2
WET: R46.1; also elsewhere on the board

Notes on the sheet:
Title:
Date:
Sheet:
(c) 2022 Expert Sleepers Ltd
